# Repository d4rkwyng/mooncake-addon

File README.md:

# Mooncake Shitty Addon

A #badgelife shitty addon PCB inspired by Mooncake from Final Space, designed for DEF CON 26.

Created by @d4rkwyng. Thanks to [AND!XOR](https://www.andnxor.com/) and SparX for their help with this project.

## Preview

| Front | Back |
|:-:|:-:|
|  |  |

## Bill of Materials

| Ref | Component | Package | Qty |
|-----|-----------|---------|-----|
| U1 | MCP23017 (Rev A / B / C: MCP23017-E/SO; Rev C ESO: MCP23017-E/SS) | Rev A / B / C: SOIC-28 (1.27 mm pitch); Rev C ESO: SSOP-28 (0.65 mm pitch) | 1 |
| D1-D10 | LED | 1206 | 10 |
| R1-R10 | 220 ohm | 1206 | 10 |
| C1 | 0.1uF | Rev C / C ESO: 1206; Rev A / B: 0402 | 1 |
| X1 | Shitty connector | 2x2 | 1 |

## Firmware Notes

Same netlist on every revision (A, B, C, C ESO):

- I2C address **0x20** (A0, A1, A2 tied to GND); ~RESET tied to 3V3; INTA/INTB not connected
- D1-D8 are driven by GPB0-GPB7, D9 by GPA0, D10 by GPA1 (active high: GPIO -> 220 ohm -> LED -> GND)
- GPA2-GPA7 are unconnected

## Revisions

- **Rev C** — Final revision. `mooncake_RevC_ESO` is a variant of the same board whose U1 footprint is the SSOP-28 MCP23017-E/SS (`lib/MCP23017-ESS_NoSilk`), not the SOIC-28 used on plain Rev C; order the matching chip for the gerbers you fab
- **Rev B** — Updated layout and routing
- **Rev A** — Initial prototype

## Project Structure

```
mooncake-addon/
├── design/          # Artwork, silkscreen, and soldermask KiCad footprints
├── gerbers/         # Manufacturing files (Rev B, C, and C ESO)
├── lib/             # KiCad component libraries
└── mooncake_*       # Schematic, PCB, and netlist files
```

## Tools

- [KiCad](https://www.kicad.org/) — Schematic and PCB design

## License

MIT License. See [LICENSE](LICENSE) file.

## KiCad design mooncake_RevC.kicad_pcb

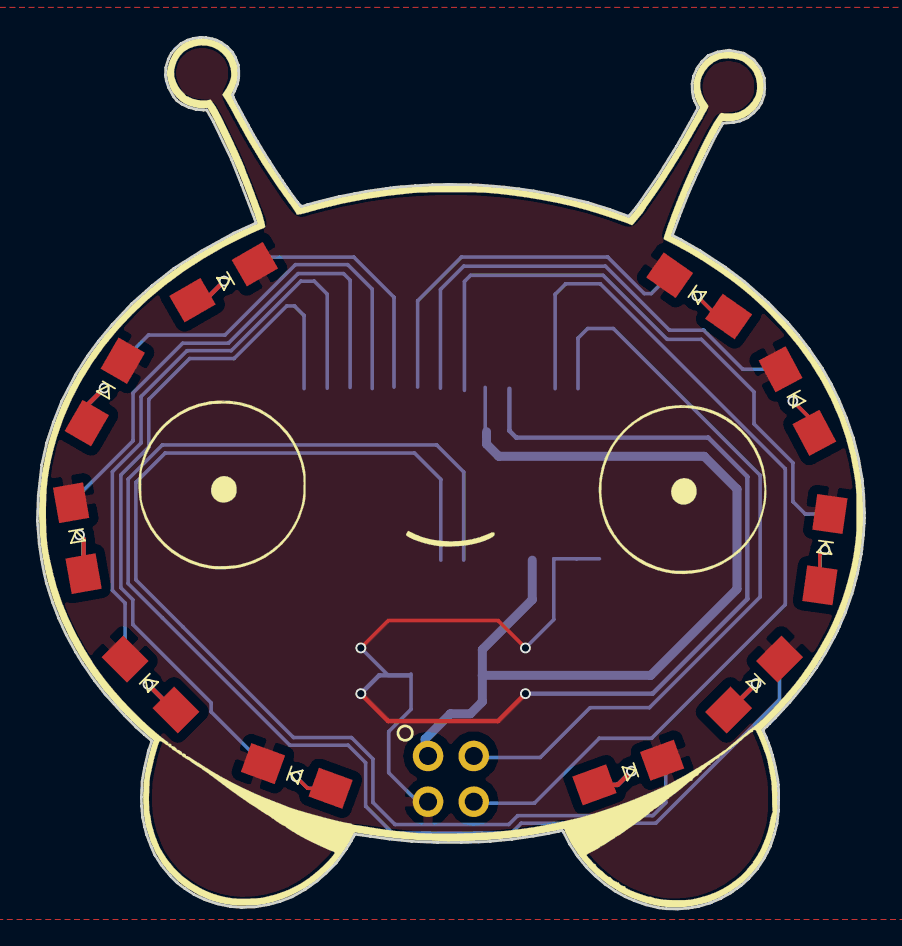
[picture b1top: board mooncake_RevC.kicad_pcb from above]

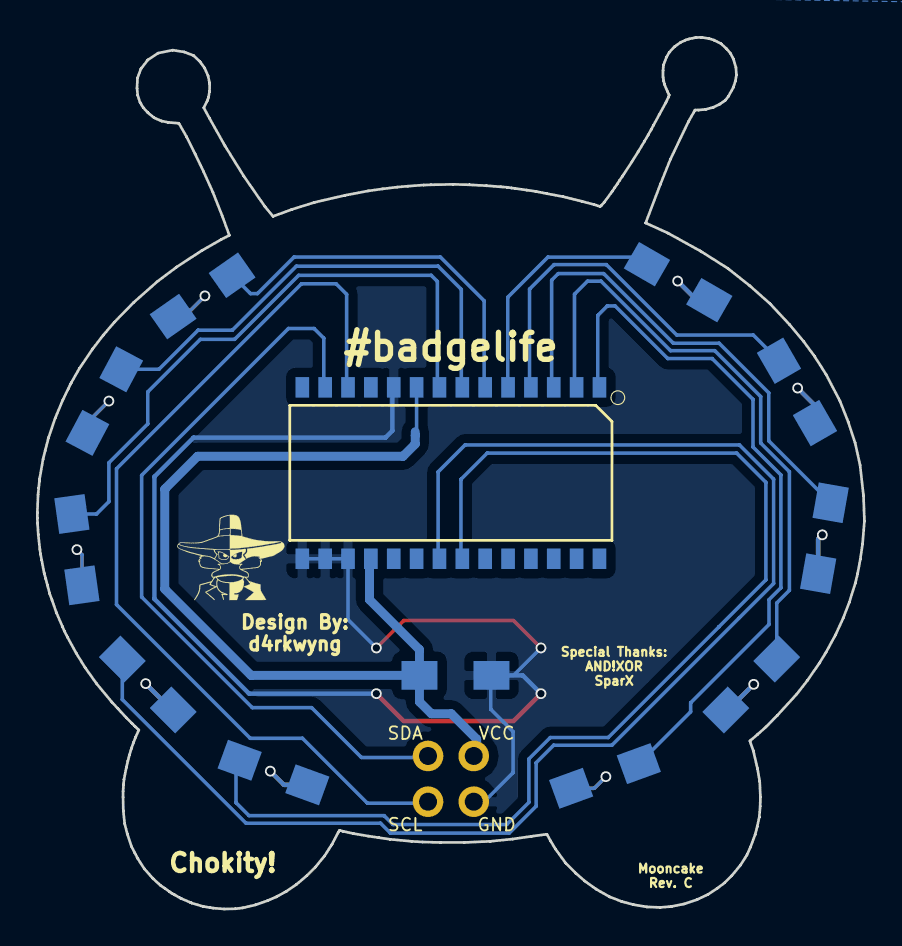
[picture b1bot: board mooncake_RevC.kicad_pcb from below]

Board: 2 copper layers, 45.9 x 48.4 mm, 23 parts (12 on the bottom side), 24 nets.

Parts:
C1: 0.1uf; C_1206_HandSoldering_NoSilk
D1, D2, D3, D4, D5, D6, D7, D8, D9, D10: LED; LED_1206_HandSoldering_MinSilk
R1, R2, R3, R4, R5, R6, R7, R8, R9, R10: 220; R_1206_HandSoldering_NoSilk
U1: MCP23017; SOIC28-1.27-17.9X7.5MM_NoSilk
X1: Badgelife_shitty_connector; Badgelife-Shitty-2x2

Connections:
+3V3: C1.1, U1.9, U1.18, X1.1
GND: C1.2, D1.1, D2.1, D3.1, D4.1, D5.1, D6.1, D7.1, D8.1, D9.1, D10.1, U1.10, U1.15, U1.16, U1.17, X1.2
unnamed: D1.2, R1.2
unnamed: D2.2, R2.2
unnamed: D3.2, R3.2
unnamed: D4.2, R4.2
unnamed: D5.2, R5.2
unnamed: D6.2, R6.2
unnamed: D7.2, R7.2
unnamed: D8.2, R8.2
unnamed: D9.2, R9.2
unnamed: D10.2, R10.2
unnamed: R1.1, U1.1
unnamed: R2.1, U1.2
unnamed: R3.1, U1.3
unnamed: R4.1, U1.4
unnamed: R5.1, U1.5
unnamed: R6.1, U1.6
unnamed: R7.1, U1.7
unnamed: R8.1, U1.8
unnamed: R9.1, U1.21
unnamed: R10.1, U1.22
scl: U1.12, X1.3
sda: U1.13, X1.4

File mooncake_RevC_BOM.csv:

"Id";"Designator";"Package";"Quantity";"Designation";"Supplier and ref";
1;"G***";"mooncake-soldermask";1;"LOGO";;;
2;"X1";"Badgelife-Shitty-2x2";1;"Badgelife_shitty_connector";;;
3;"R9,R10,R8,R7,R6,R5,R4,R3,R2,R1";"R_1206_HandSoldering_NoSilk";10;"220";;;
4;"D10,D1,D2,D3,D4,D5,D6,D7,D8,D9";"LED_1206_HandSoldering_MinSilk";10;"LED";;;
5;"G***";"mooncake-silkscreen";1;"LOGO";;;
6;"C1";"C_1206_HandSoldering_NoSilk";1;"0.1uf";;;
7;"U1";"SOIC28-1.27-17.9X7.5MM_NoSilk";1;"MCP23017";;;
8;"G***";"gary_soldermask";1;"LOGO";;;
9;"G***";"d4rkwyng";1;"LOGO";;;
10;"G***";"d4rkwyng_solder";1;"LOGO";;;

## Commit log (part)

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2018-05-31 Initial Project
2018-05-31 Issues with EdgeCuts
2018-06-01 Updated Traces
    Gerbers included
2018-06-01 Example Gerbers
2018-06-01 Revision B
2018-06-01 Rev B tweaks
2018-06-02 Rev B Examples
2018-06-02 ReadMe Update
2018-06-02 Readme updates
2018-06-02 Rev B Updates
2018-06-06 Update to Naming Structure
2018-06-13 Revision C
2018-06-13 Gerbers
2018-06-13 Raw Gary Update
2018-06-13 The terror that flaps in the night!
2018-06-18 RevC update and ESO version
